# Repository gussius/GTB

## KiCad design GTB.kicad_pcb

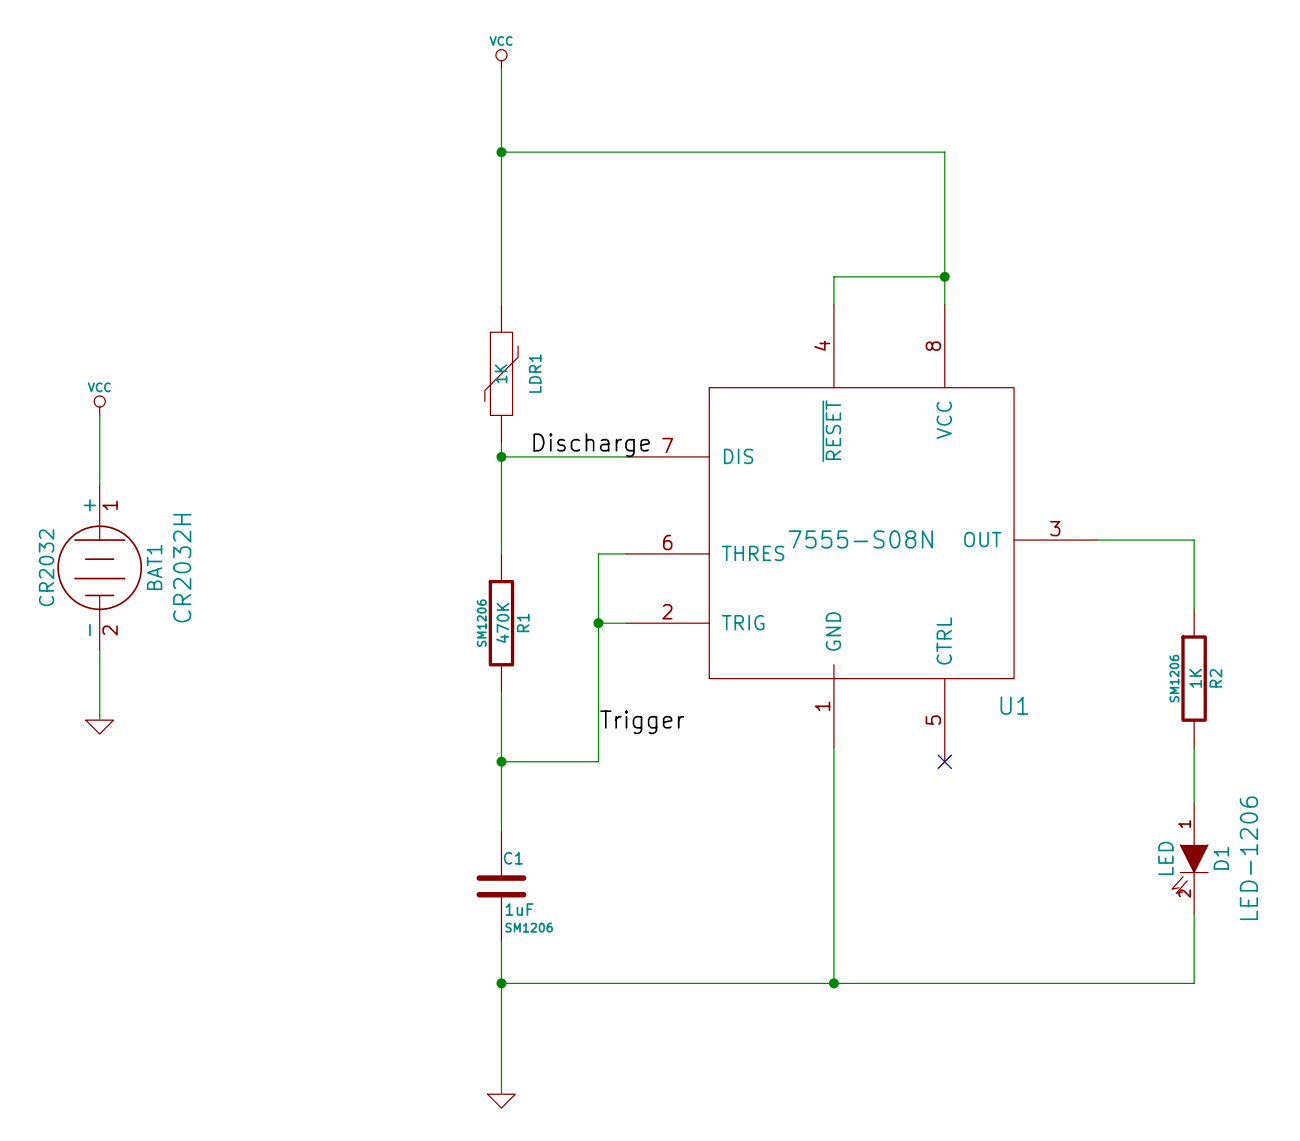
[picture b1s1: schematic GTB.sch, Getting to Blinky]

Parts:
BAT1: CR2032; CR2032H
C1: 1uF; SM1206
D1: LED; LED-1206
LDR1: 1K
R1: 470K; SM1206
R2: 1K; SM1206
U1: 7555-S08N; S08N

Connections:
/Discharge: LDR1.2, R1.1, U1.7 (DIS)
/Trigger: C1.1, R1.2, U1.2 (TRIG), U1.6 (THRES)
GND: BAT1.2 (-), C1.2, D1.2 (K), U1.1 (GND)
unnamed: R2.1, U1.3 (OUT)
unnamed: D1.1 (A), R2.2
VCC: BAT1.1 (+), LDR1.1, U1.4 (~RESET), U1.8 (VCC)

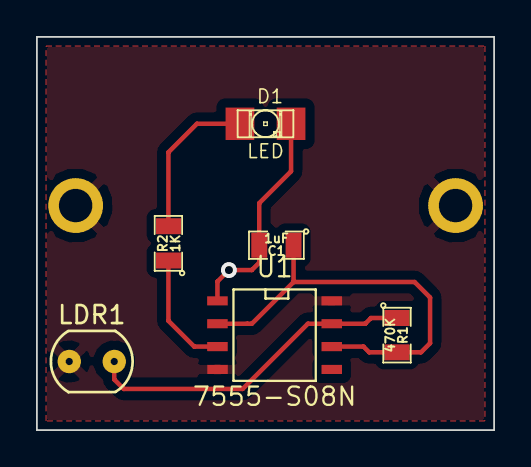
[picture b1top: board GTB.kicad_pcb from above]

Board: 2 copper layers, 25.4 x 21.8 mm, 8 parts (1 on the bottom side), 6 nets.

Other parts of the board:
VAL: ScriptScript3

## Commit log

2014-02-02 First commit to github for Getting To Blinky Hardware.
2014-02-02 Finally finished GTB
    Getting To Blinky board finally finished. The Solder mask relief is a
    bit grainy though. Needs a higher resolution bitmap.
